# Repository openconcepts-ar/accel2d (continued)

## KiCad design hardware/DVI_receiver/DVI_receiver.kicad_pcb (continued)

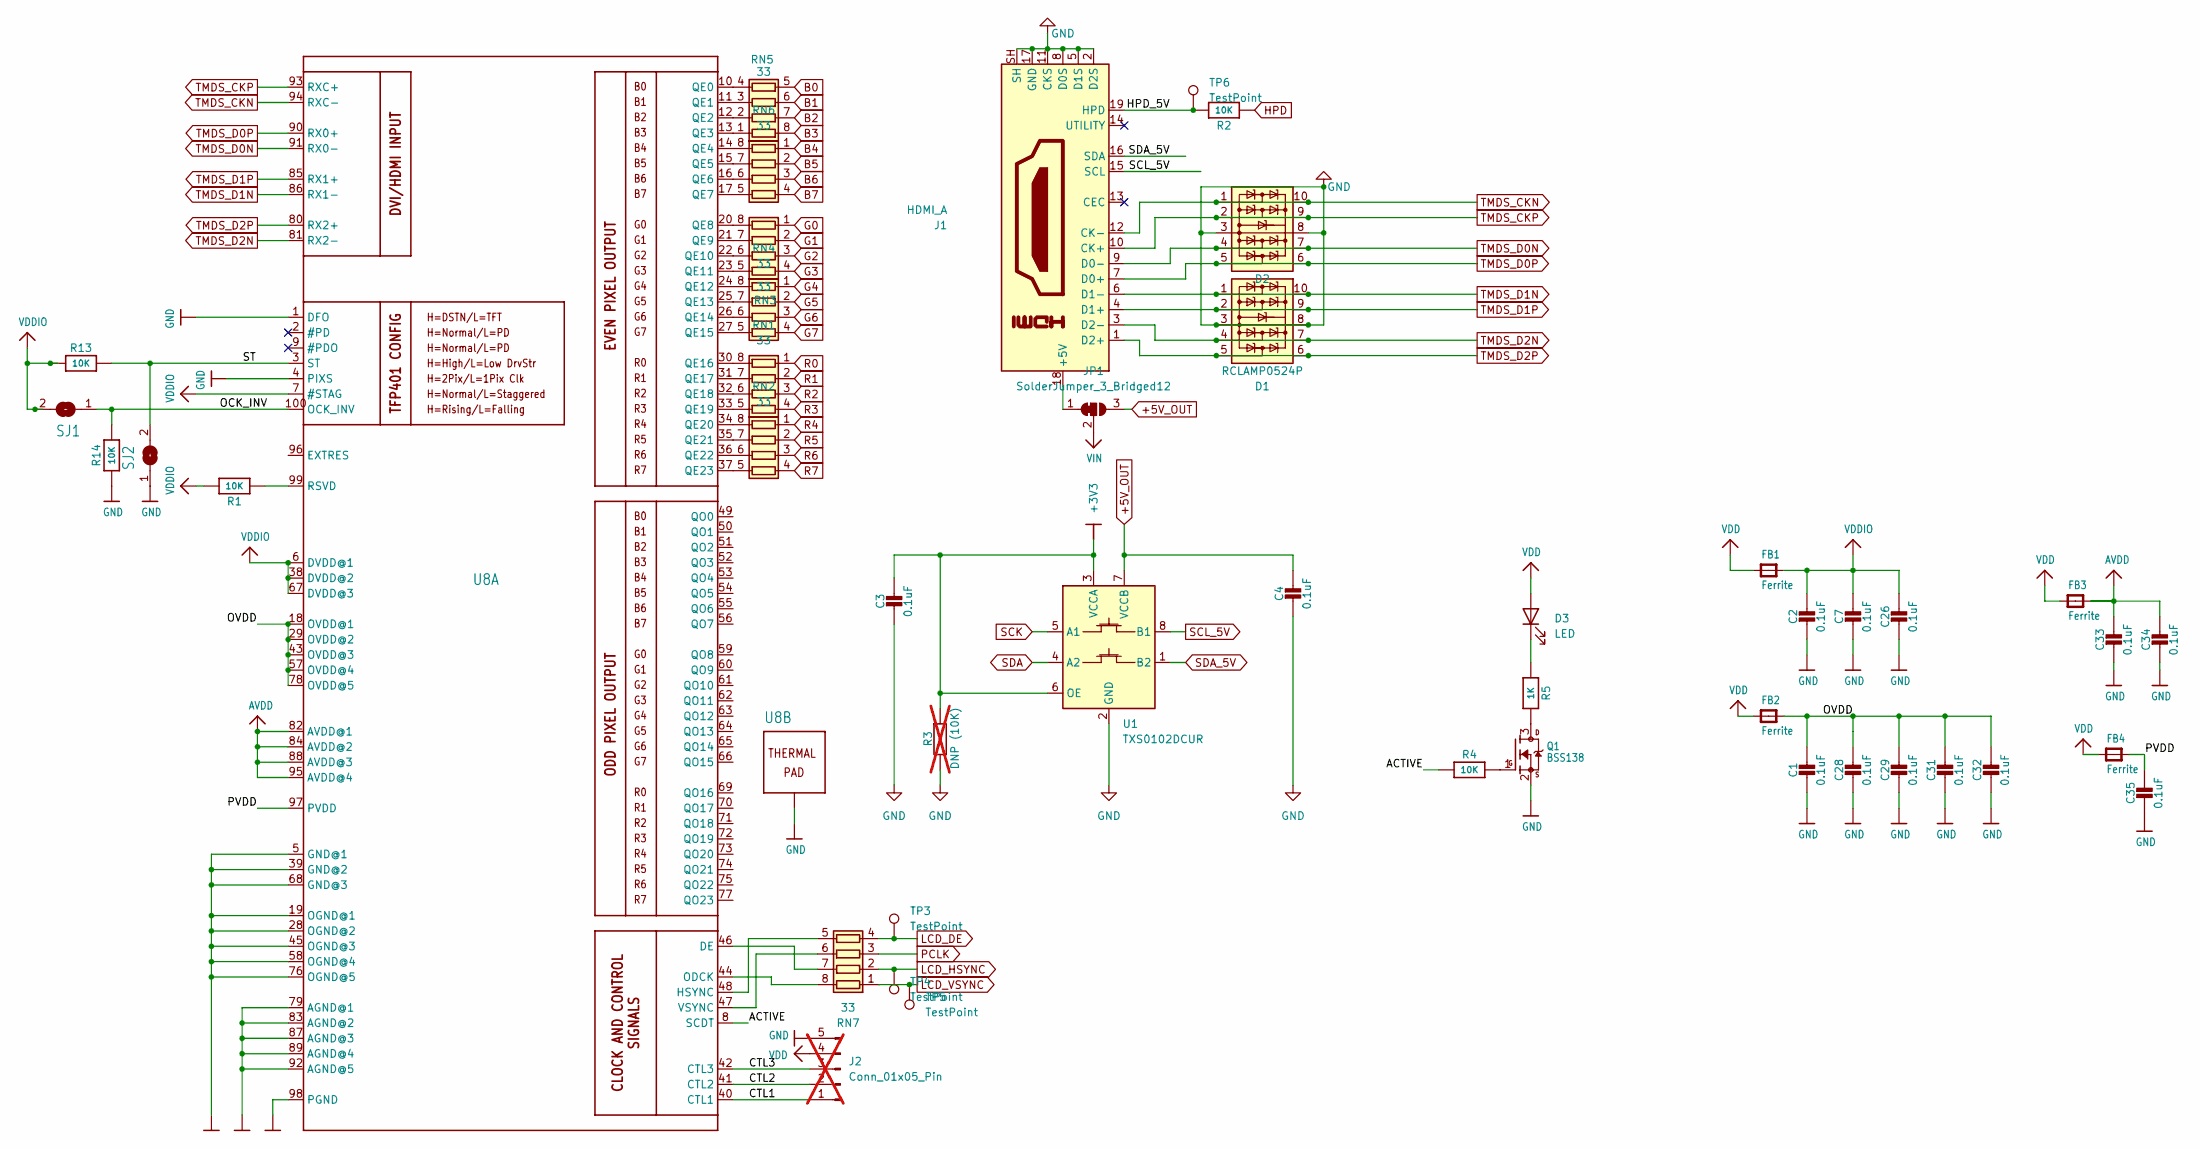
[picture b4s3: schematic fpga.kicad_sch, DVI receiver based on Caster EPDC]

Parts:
C1, C2, C3, C4, C7, C26, C28, C29, C31, C32, C33, C34, C35: 0.1uF; C_0603_1608Metric
D1, D2: RCLAMP0524P; Diodes_UDFN-10_1.0x2.5mm_P0.5mm; MPN RCLAMP0524P
D3: LED; LED_0603_1608Metric
FB1, FB2, FB3, FB4: Ferrite; L_0603_1608Metric; MPN BLM18RK601SN1D
J1: HDMI_A; HDMI_A_Amphenol_10029449-x01xLF_Horizontal; MPN 10029449-111RLF; LCSC Part Number C427307
J2: Conn_01x05_Pin; PinHeader_1x05_P1.27mm_Vertical; not fitted
JP1: SolderJumper_3_Bridged12; SolderJumper-3_P1.3mm_Bridged12_RoundedPad1.0x1.5mm
Q1: BSS138; SOT-323_SC-70; MPN BSS138PW,115
R1, R2, R4, R13, R14: 10K; R_0402_1005Metric
R3: DNP (10K); R_0402_1005Metric; LCSC Part Number C25531; not fitted
R5: 1K; R_0402_1005Metric
RN1, RN2, RN3, RN4, RN5, RN6, RN7: 33; R_Array_Convex_4x0402; MPN YC124-JR-0733RL
SJ1, SJ2: SOLDERJUMPER; SolderJumper-2_P1.3mm_Bridged_RoundedPad1.0x1.5mm
TP3, TP4, TP5, TP6: TestPoint; TestPoint_Pad_D1.0mm
U1: TXS0102DCUR; VSSOP-8_2.3x2mm_P0.5mm; MPN TXS0102DCUR
U8: TFP401; TQFP-100-1EP_14x14mm_P0.5mm_EP5x5mm_ThermalVias; MPN TFP401APZPR

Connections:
+5V_OUT: C4.1, JP1.3 (B), U1.7 (VCCB); also elsewhere on the board
/fpga/ACTIVE: R4.1, U8.8 (SCDT)
/fpga/CTL1: J2.1, U8.40 (CTL1)
/fpga/CTL2: J2.2, U8.41 (CTL2)
/fpga/CTL3: J2.3, U8.42 (CTL3)
/fpga/HPD_5V: J1.19 (HPD), R2.2, TP6.1
/fpga/OCK_INV: R14.2, SJ1.1, U8.100 (OCK_INV)
/fpga/OVDD: C1.1, C28.1, C29.1, C31.1, C32.1, FB2.2, U8.18 (OVDD@1), U8.29 (OVDD@2), U8.43 (OVDD@3), U8.57 (OVDD@4), U8.78 (OVDD@5)
/fpga/PVDD: C35.1, FB4.2, U8.97 (PVDD)
/fpga/ST: R13.2, SJ2.2, U8.3 (ST)
AVDD: C33.1, C34.1, FB3.2, U8.82 (AVDD@1), U8.84 (AVDD@2), U8.88 (AVDD@3), U8.95 (AVDD@4)
B0: RN5.5 (R4.2); also elsewhere on the board
B1: RN5.6 (R3.2); also elsewhere on the board
B2: RN5.7 (R2.2); also elsewhere on the board
B3: RN5.8 (R1.2); also elsewhere on the board
B4: RN6.1 (R1.1); also elsewhere on the board
B5: RN6.2 (R2.1); also elsewhere on the board
B6: RN6.3 (R3.1); also elsewhere on the board
B7: RN6.4 (R4.1); also elsewhere on the board
G0: RN3.1 (R1.1); also elsewhere on the board
G1: RN3.2 (R2.1); also elsewhere on the board
G2: RN3.3 (R3.1); also elsewhere on the board
G3: RN3.4 (R4.1); also elsewhere on the board
G4: RN4.1 (R1.1); also elsewhere on the board
G5: RN4.2 (R2.1); also elsewhere on the board
G6: RN4.3 (R3.1); also elsewhere on the board
G7: RN4.4 (R4.1); also elsewhere on the board
GND: C1.2, C2.2, C3.2, C4.2, C7.2, C26.2, C28.2, C29.2, C31.2, C32.2, C33.2, C34.2, C35.2, D1.3 (GND), D1.8 (GND), D2.3 (GND), D2.8 (GND), J1.2 (D2S), J1.5 (D1S), J1.8 (D0S), J1.11 (CKS), J1.17 (GND), J1.SH, J2.5, Q1.2 (S), R3.2, R14.1, SJ2.1, U1.2 (GND), U8.1 (DFO), U8.4 (PIXS), U8.5 (GND@1), U8.19 (OGND@1), U8.28 (OGND@2), U8.39 (GND@2), U8.45 (OGND@3), U8.58 (OGND@4), U8.68 (GND@3), U8.76 (OGND@5), U8.79 (AGND@1), U8.83 (AGND@2), U8.87 (AGND@3), U8.89 (AGND@4), U8.92 (AGND@5), U8.98 (PGND), U8.P$1 (TP), U8.P$2 (TP), U8.P$3 (TP), U8.P$4 (TP), U8.P$5 (TP), U8.P$6 (TP), U8.P$7 (TP), U8.P$8 (TP), U8.P$9 (TP), U8.P$10 (TP), U8.P$11 (TP), U8.P$12 (TP), U8.P$13 (TP), U8.P$14 (TP), U8.P$15 (TP), U8.P$16 (TP), U8.THERMAL (TP); also elsewhere on the board
HPD: R2.1; also elsewhere on the board
LCD_DE: RN7.4 (R4.1), TP3.1; also elsewhere on the board
LCD_HSYNC: RN7.2 (R2.1), TP4.1; also elsewhere on the board
LCD_VSYNC: RN7.1 (R1.1), TP5.1; also elsewhere on the board
unnamed: D3.1 (K), R5.1
unnamed: J1.18 (+5V), JP1.1 (A)
unnamed: Q1.3 (D), R5.2
unnamed: Q1.1 (G), R4.2
unnamed: RN1.8 (R1.2), U8.30 (QE16)
unnamed: RN1.7 (R2.2), U8.31 (QE17)
unnamed: RN1.6 (R3.2), U8.32 (QE18)
unnamed: RN1.5 (R4.2), U8.33 (QE19)
unnamed: RN2.8 (R1.2), U8.34 (QE20)
unnamed: RN2.7 (R2.2), U8.35 (QE21)
unnamed: RN2.6 (R3.2), U8.36 (QE22)
unnamed: RN2.5 (R4.2), U8.37 (QE23)
unnamed: RN3.8 (R1.2), U8.20 (QE8)
unnamed: RN3.7 (R2.2), U8.21 (QE9)
unnamed: RN3.6 (R3.2), U8.22 (QE10)
unnamed: RN3.5 (R4.2), U8.23 (QE11)
unnamed: RN4.8 (R1.2), U8.24 (QE12)
unnamed: RN4.7 (R2.2), U8.25 (QE13)
unnamed: RN4.6 (R3.2), U8.26 (QE14)
unnamed: RN4.5 (R4.2), U8.27 (QE15)
unnamed: RN5.1 (R1.1), U8.13 (QE3)
unnamed: RN5.2 (R2.1), U8.12 (QE2)
unnamed: RN5.3 (R3.1), U8.11 (QE1)
unnamed: RN5.4 (R4.1), U8.10 (QE0)
unnamed: RN6.8 (R1.2), U8.14 (QE4)
unnamed: RN6.7 (R2.2), U8.15 (QE5)
unnamed: RN6.6 (R3.2), U8.16 (QE6)
unnamed: RN6.5 (R4.2), U8.17 (QE7)
unnamed: RN7.8 (R1.2), U8.44 (ODCK)
unnamed: RN7.7 (R2.2), U8.46 (DE)
unnamed: RN7.6 (R3.2), U8.47 (VSYNC)
unnamed: RN7.5 (R4.2), U8.48 (HSYNC)
unnamed: R1.1, U8.99 (RSVD)
PCLK: RN7.3 (R3.1); also elsewhere on the board
R0: RN1.1 (R1.1); also elsewhere on the board
R1: RN1.2 (R2.1); also elsewhere on the board
R2: RN1.3 (R3.1); also elsewhere on the board
R3: RN1.4 (R4.1); also elsewhere on the board
R4: RN2.1 (R1.1); also elsewhere on the board
R5: RN2.2 (R2.1); also elsewhere on the board
R6: RN2.3 (R3.1); also elsewhere on the board
R7: RN2.4 (R4.1); also elsewhere on the board
SCK: U1.5 (A1); also elsewhere on the board
SCL_5V: J1.15 (SCL), U1.8 (B1)
SDA: U1.4 (A2); also elsewhere on the board
SDA_5V: J1.16 (SDA), U1.1 (B2)
TMDS_CKN: D2.1 (IO1), D2.10 (NC4), J1.12 (CK-), U8.94 (RXC-)
TMDS_CKP: D2.2 (IO2), D2.9 (NC3), J1.10 (CK+), U8.93 (RXC+)
TMDS_D0N: D2.4 (IO3), D2.7 (NC2), J1.9 (D0-), U8.91 (RX0-)
TMDS_D0P: D2.5 (IO4), D2.6 (NC1), J1.7 (D0+), U8.90 (RX0+)
TMDS_D1N: D1.1 (IO1), D1.10 (NC4), J1.6 (D1-), U8.86 (RX1-)
TMDS_D1P: D1.2 (IO2), D1.9 (NC3), J1.4 (D1+), U8.85 (RX1+)
TMDS_D2N: D1.4 (IO3), D1.7 (NC2), J1.3 (D2-), U8.81 (RX2-)
TMDS_D2P: D1.5 (IO4), D1.6 (NC1), J1.1 (D2+), U8.80 (RX2+)
VDDIO: C2.1, C7.1, C26.1, FB1.2, R1.2, R13.1, SJ1.2, U8.6 (DVDD@1), U8.7 (#STAG), U8.38 (DVDD@2), U8.67 (DVDD@3)
VIN: JP1.2 (C); also elsewhere on the board
VIO: C3.1, D3.2 (A), FB1.1, FB2.1, FB3.1, FB4.1, J2.4, R3.1, U1.3 (VCCA), U1.6 (OE); also elsewhere on the board

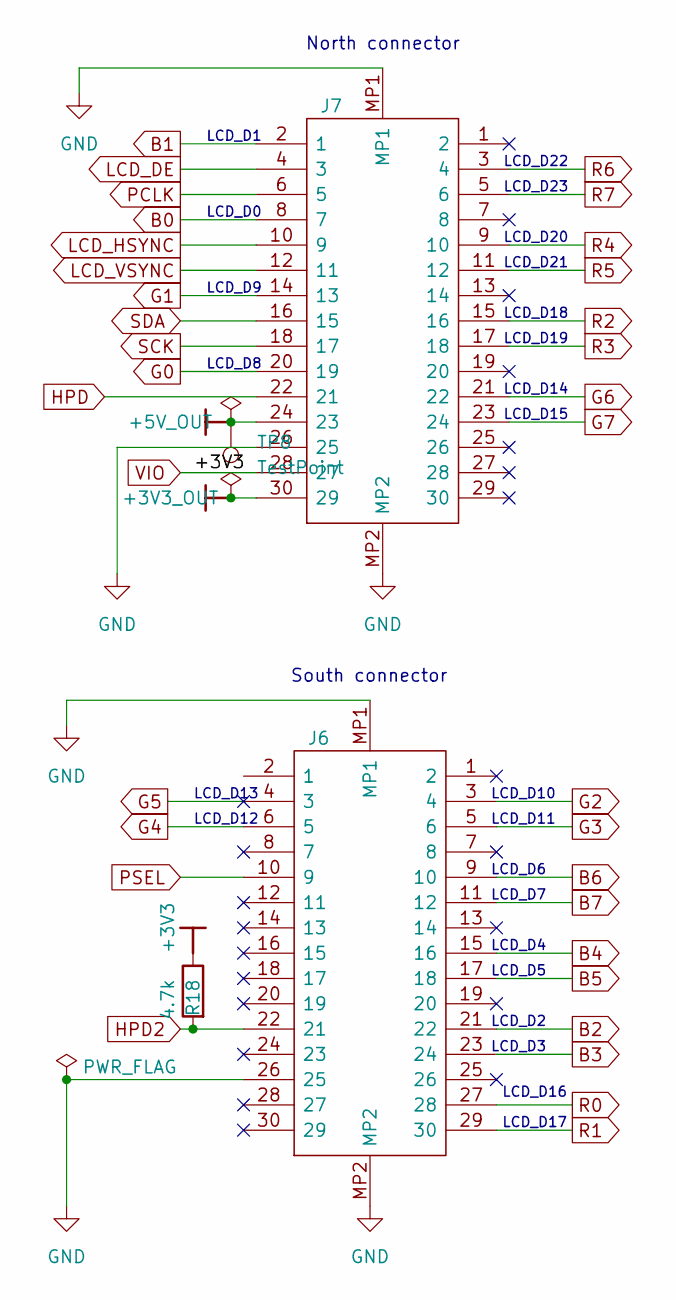
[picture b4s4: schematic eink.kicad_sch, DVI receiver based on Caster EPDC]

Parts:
J6, J7: DF12NB(3.0)-30DS-0.5V(51); DF12NB3030DP05V51; MPN DF12NB(3.0)-30DS-0.5V(51)
R18: 4.7k; R_0402_1005Metric; LCSC Part Number C25940
TP8: TestPoint; TestPoint_Pad_D1.0mm

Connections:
+3V3_OUT: J7.30 (29); also elsewhere on the board
+5V_OUT: J7.24 (23), TP8.1; also elsewhere on the board
B0: J7.8 (7); also elsewhere on the board
B1: J7.2 (1); also elsewhere on the board
B2: J6.21 (22); also elsewhere on the board
B3: J6.23 (24); also elsewhere on the board
B4: J6.15 (16); also elsewhere on the board
B5: J6.17 (18); also elsewhere on the board
B6: J6.9 (10); also elsewhere on the board
B7: J6.11 (12); also elsewhere on the board
G0: J7.20 (19); also elsewhere on the board
G1: J7.14 (13); also elsewhere on the board
G2: J6.3 (4); also elsewhere on the board
G3: J6.5 (6); also elsewhere on the board
G4: J6.6 (5); also elsewhere on the board
G5: J6.4 (3); also elsewhere on the board
G6: J7.21 (22); also elsewhere on the board
G7: J7.23 (24); also elsewhere on the board
GND: J6.26 (25), J6.MP1, J6.MP2, J7.26 (25), J7.MP1, J7.MP2; also elsewhere on the board
HPD: J7.22 (21); also elsewhere on the board
HPD2: J6.22 (21), R18.2
LCD_DE: J7.4 (3); also elsewhere on the board
LCD_HSYNC: J7.10 (9); also elsewhere on the board
LCD_VSYNC: J7.12 (11); also elsewhere on the board
PCLK: J7.6 (5); also elsewhere on the board
PSEL: J6.10 (9)
R0: J6.27 (28); also elsewhere on the board
R1: J6.29 (30); also elsewhere on the board
R2: J7.15 (16); also elsewhere on the board
R3: J7.17 (18); also elsewhere on the board
R4: J7.9 (10); also elsewhere on the board
R5: J7.11 (12); also elsewhere on the board
R6: J7.3 (4); also elsewhere on the board
R7: J7.5 (6); also elsewhere on the board
SCK: J7.18 (17); also elsewhere on the board
SDA: J7.16 (15); also elsewhere on the board
VIO: J7.28 (27), R18.1; also elsewhere on the board

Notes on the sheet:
LCD_D17
LCD_D0
LCD_D16
South connector
LCD_D11
LCD_D4
LCD_D3
LCD_D8
LCD_D10
LCD_D19
LCD_D23
LCD_D20
North connector
LCD_D5
LCD_D13
LCD_D18
LCD_D21
LCD_D22
LCD_D7
LCD_D6
LCD_D15
LCD_D1
LCD_D12
LCD_D9
LCD_D2
LCD_D14

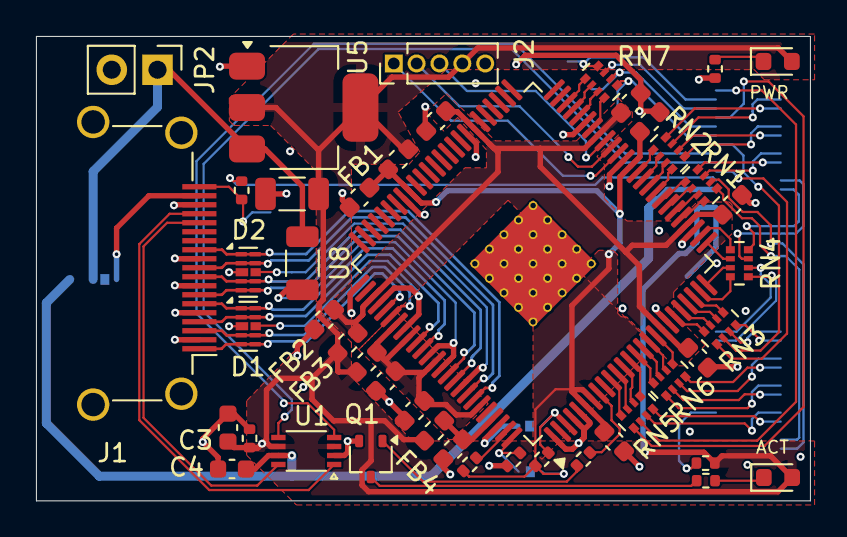
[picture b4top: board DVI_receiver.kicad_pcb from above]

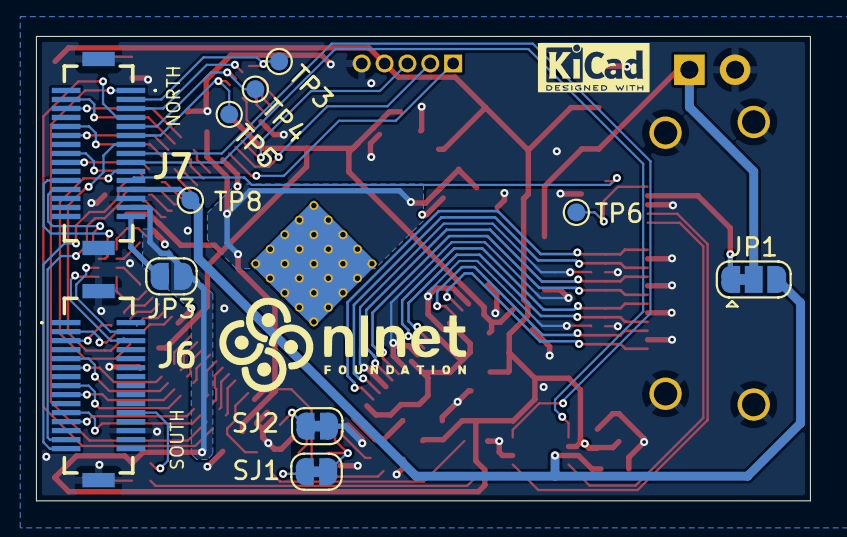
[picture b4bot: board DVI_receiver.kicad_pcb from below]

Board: 4 copper layers, 43.0 x 25.8 mm, 57 parts (11 on the bottom side), 92 nets.

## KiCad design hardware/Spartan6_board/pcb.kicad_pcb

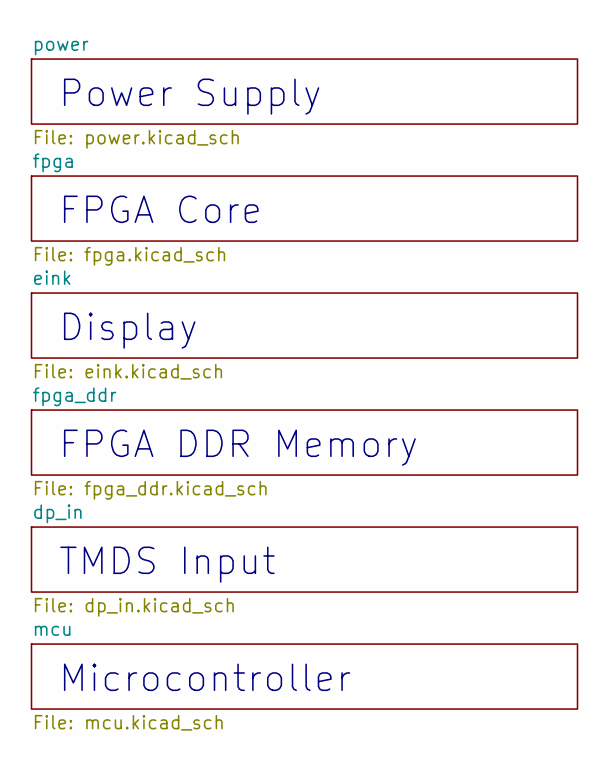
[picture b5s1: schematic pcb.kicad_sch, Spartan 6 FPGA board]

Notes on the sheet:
FPGA DDR Memory
Power Supply
Microcontroller
Display
FPGA Core
TMDS Input

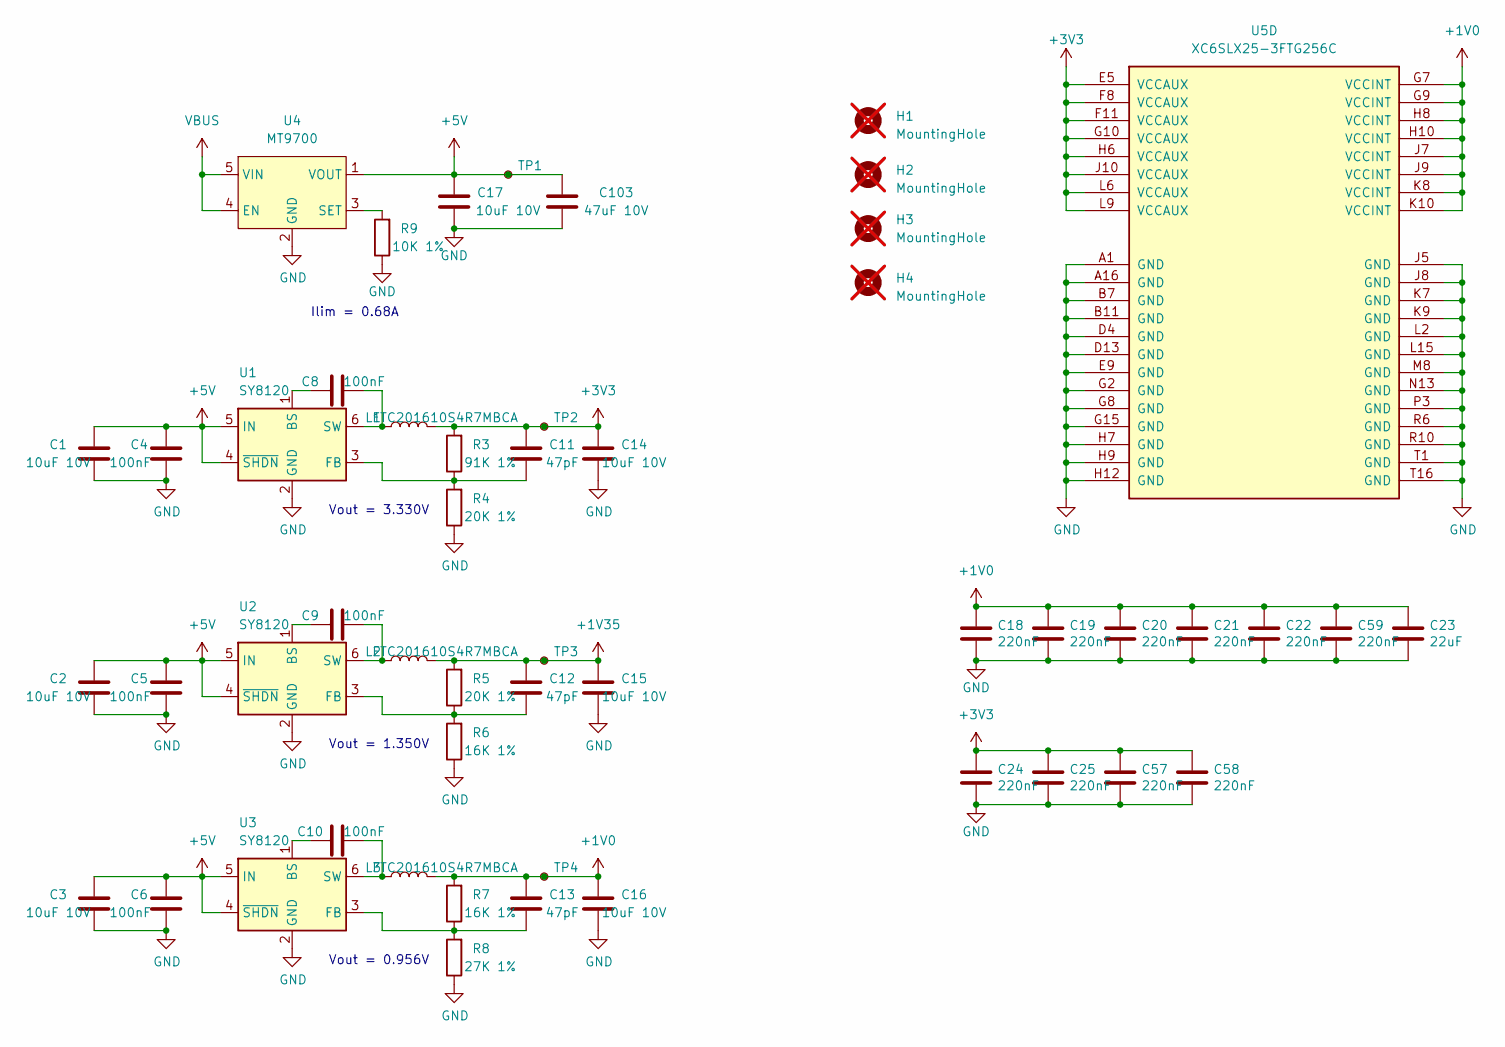
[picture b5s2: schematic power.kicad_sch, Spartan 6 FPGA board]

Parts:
C1, C2, C3, C14, C15, C16: 10uF 10V; C_0805_2012Metric
C4, C5, C6, C8, C9, C10: 100nF; C_0402_1005Metric
C11, C12, C13: 47pF; C_0402_1005Metric
C17: 10uF 10V; C_0805_2012Metric; LCSC Part Number C32635
C18, C19, C20, C21, C22, C24, C25, C57, C58, C59: 220nF; C_0402_1005Metric; LCSC C880414
C23: 22uF; C_0603_1608Metric; LCSC Part Number C86295
C103: 47uF 10V; C_1206_3216Metric; LCSC Part Number C96123
H1, H2, H3, H4: MountingHole; MountingHole_2.2mm_M2_DIN965; not fitted
L1, L2, L3: FTC201610S4R7MBCA; L_Murata_DFE201610P; MPN FTC201610S4R7MBCA
R3: 91K 1%; R_0402_1005Metric
R4, R5: 20K 1%; R_0402_1005Metric; LCSC Part Number WR04X2002FTL
R6, R7: 16K 1%; R_0402_1005Metric
R8: 27K 1%; R_0402_1005Metric
R9: 10K 1%; R_0402_1005Metric
TP1, TP2, TP3, TP4: TestPoint_Small; TestPoint_Pad_D1.5mm
U1, U2, U3: SY8120; SOT-23-6; MPN SY8120IABC
U4: MT9700; SOT-23-5; MPN MT9700
U5: XC6SLX25-3FTG256C; Xilinx_FTG256; LCSC Part Number C1521716

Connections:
+1V0: C13.2, C16.2, C18.1, C19.1, C20.1, C21.1, C22.1, C23.1, C59.1, L3.2, R7.2, TP4.1, U5.G7 (VCCINT), U5.G9 (VCCINT), U5.H8 (VCCINT), U5.H10 (VCCINT), U5.J7 (VCCINT), U5.J9 (VCCINT), U5.K8 (VCCINT), U5.K10 (VCCINT)
+1V35: C12.2, C15.2, L2.2, R5.2, TP3.1; also elsewhere on the board
+3V3: C11.2, C14.2, C24.1, C25.1, C57.1, C58.1, L1.2, R3.2, TP2.1, U5.E5 (VCCAUX), U5.F8 (VCCAUX), U5.F11 (VCCAUX), U5.G10 (VCCAUX), U5.H6 (VCCAUX), U5.J10 (VCCAUX), U5.L6 (VCCAUX), U5.L9 (VCCAUX); also elsewhere on the board
+5V: C1.2, C2.2, C3.2, C4.2, C5.2, C6.2, C17.2, C103.2, TP1.1, U1.4 (~SHDN), U1.5 (IN), U2.4 (~SHDN), U2.5 (IN), U3.4 (~SHDN), U3.5 (IN), U4.1 (VOUT); also elsewhere on the board
GND: C1.1, C2.1, C3.1, C4.1, C5.1, C6.1, C14.1, C15.1, C16.1, C17.1, C18.2, C19.2, C20.2, C21.2, C22.2, C23.2, C24.2, C25.2, C57.2, C58.2, C59.2, C103.1, R4.1, R6.1, R8.1, R9.1, U1.2 (GND), U2.2 (GND), U3.2 (GND), U4.2 (GND), U5.A1 (GND), U5.A16 (GND), U5.B7 (GND), U5.B11 (GND), U5.D4 (GND), U5.D13 (GND), U5.E9 (GND), U5.G2 (GND), U5.G8 (GND), U5.G15 (GND), U5.H7 (GND), U5.H9 (GND), U5.H12 (GND), U5.J5 (GND), U5.J8 (GND), U5.K7 (GND), U5.K9 (GND), U5.L2 (GND), U5.L15 (GND), U5.M8 (GND), U5.N13 (GND), U5.P3 (GND), U5.R6 (GND), U5.R10 (GND), U5.T1 (GND), U5.T16 (GND); also elsewhere on the board
unnamed: C8.2, U1.1 (BS)
unnamed: C11.1, R3.1, R4.2, U1.3 (FB)
unnamed: C8.1, L1.1, U1.6 (SW)
unnamed: C9.2, U2.1 (BS)
unnamed: C12.1, R5.1, R6.2, U2.3 (FB)
unnamed: C9.1, L2.1, U2.6 (SW)
unnamed: C10.2, U3.1 (BS)
unnamed: C13.1, R7.1, R8.2, U3.3 (FB)
unnamed: C10.1, L3.1, U3.6 (SW)
unnamed: R9.2, U4.3 (SET)
VBUS: U4.4 (EN), U4.5 (VIN); also elsewhere on the board

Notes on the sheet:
Vout = 1.350V
Ilim = 0.68A
Vout = 0.956V
Vout = 3.330V

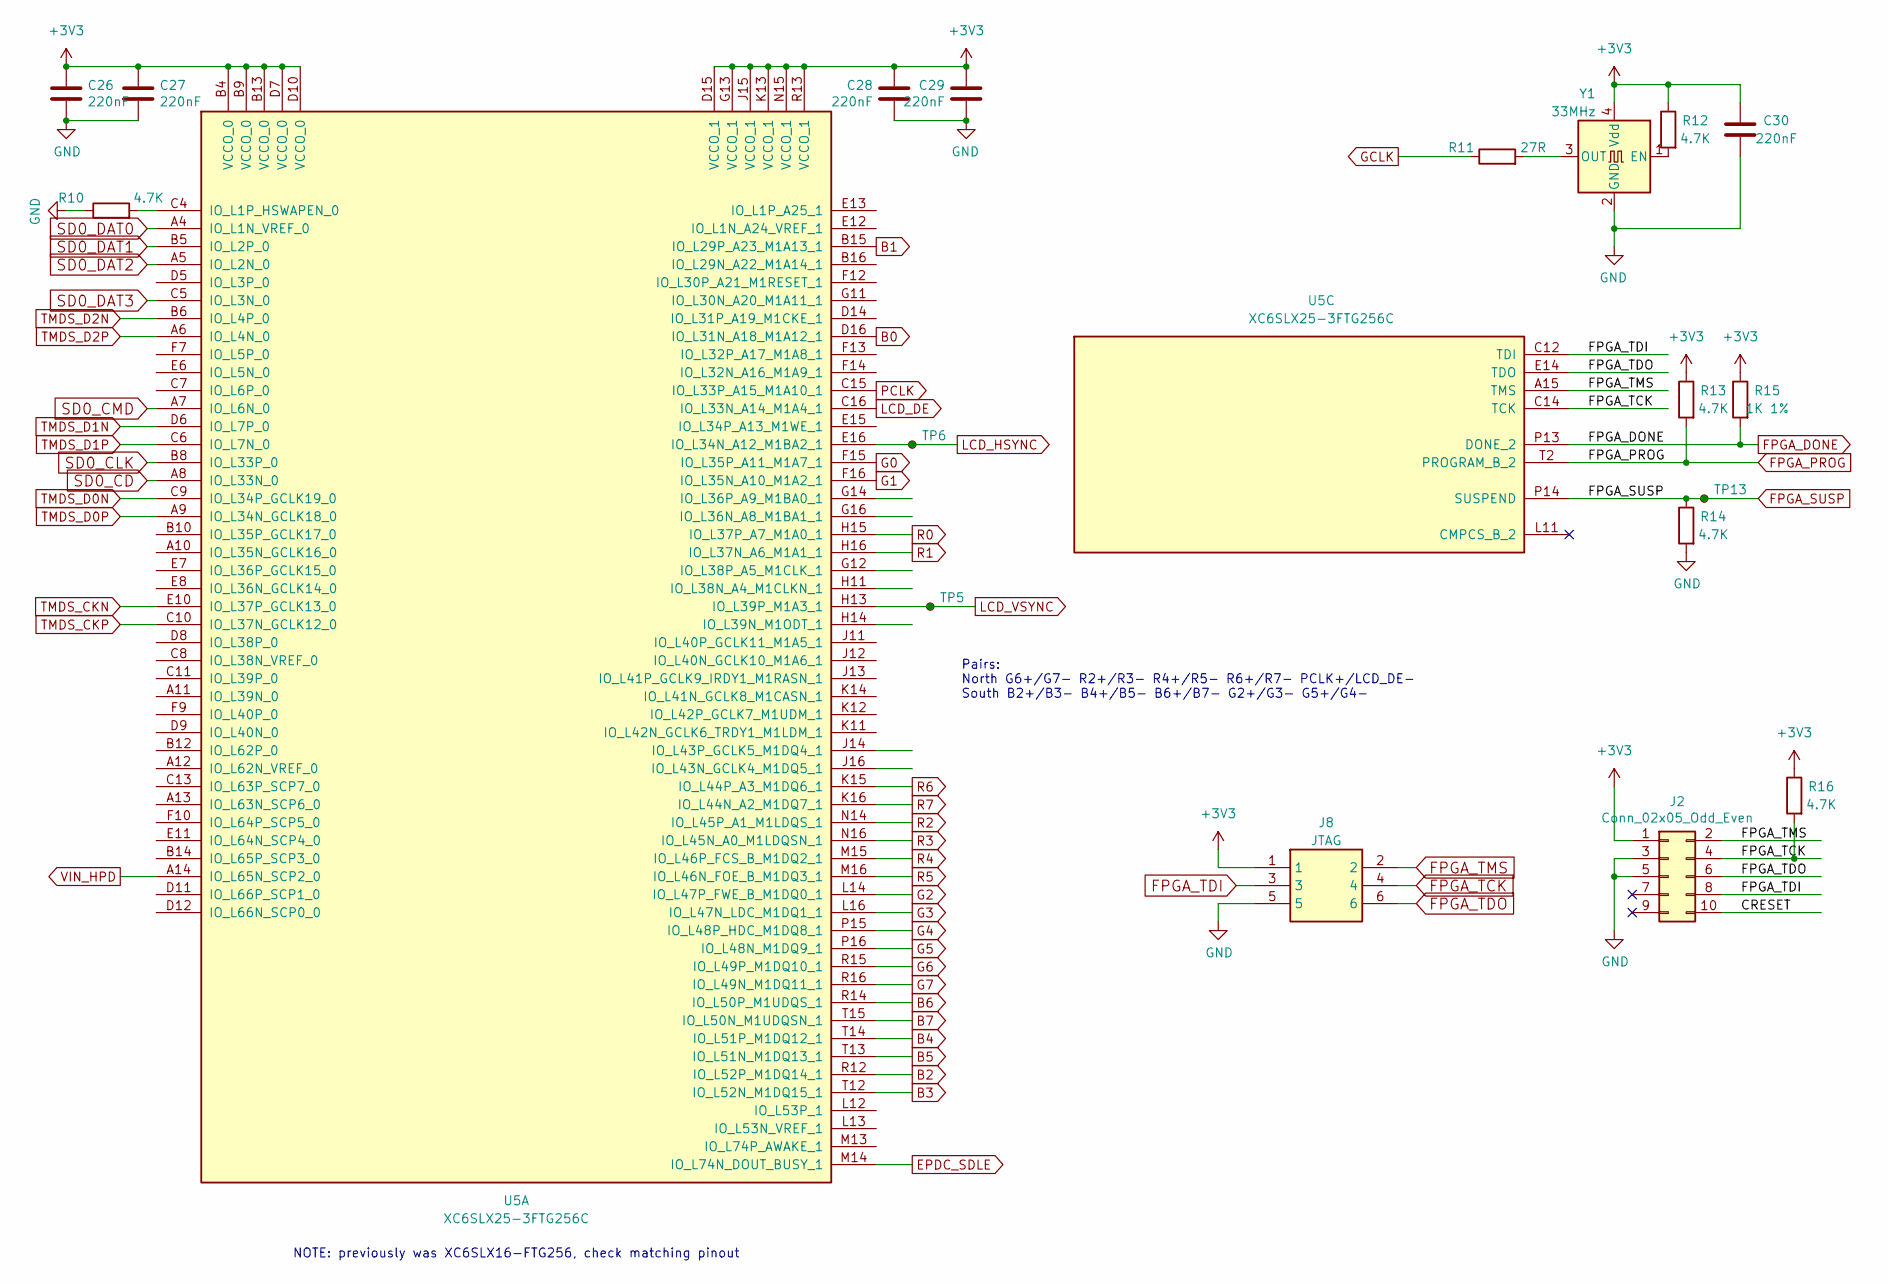
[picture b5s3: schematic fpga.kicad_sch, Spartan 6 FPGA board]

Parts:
C26, C27, C28, C29, C30: 220nF; C_0402_1005Metric; LCSC C880414
J2: Conn_02x05_Odd_Even; PinHeader_2x05_P1.27mm_Vertical_SMD
J8: JTAG; Tag-Connect_TC2030-IDC-NL_2x03_P1.27mm_Vertical; Mouser Part Number 474-PRT-12807; LCSC Part Number DNP
R10, R12, R13, R14, R16: 4.7K; R_0402_1005Metric; LCSC C105870
R11: 27R; R_0402_1005Metric; LCSC C93929
R15: 1K 1%; R_0402_1005Metric
TP5, TP6, TP13: TestPoint_Small; TestPoint_Pad_D1.5mm
U5: XC6SLX25-3FTG256C; Xilinx_FTG256; LCSC Part Number C1521716
Y1: 33MHz; Oscillator_SMD_Abracon_ASE-4Pin_3.2x2.5mm; MPN 3N24000G33YC; LCSC Part Number C252339

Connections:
+3V3: C26.1, C27.1, C28.1, C29.1, C30.2, J2.1, J8.1, R12.1, R13.1, R15.1, R16.1, U5.B4 (VCCO_0), U5.B9 (VCCO_0), U5.B13 (VCCO_0), U5.D7 (VCCO_0), U5.D10 (VCCO_0), U5.D15 (VCCO_1), U5.G13 (VCCO_1), U5.J15 (VCCO_1), U5.K13 (VCCO_1), U5.N15 (VCCO_1), U5.R13 (VCCO_1), Y1.4 (Vdd); also elsewhere on the board
B0: U5.D16 (IO_L31N_A18_M1A12_1); also elsewhere on the board
B1: U5.B15 (IO_L29P_A23_M1A13_1); also elsewhere on the board
B2: U5.R12 (IO_L52P_M1DQ14_1); also elsewhere on the board
B3: U5.T12 (IO_L52N_M1DQ15_1); also elsewhere on the board
B4: U5.T14 (IO_L51P_M1DQ12_1); also elsewhere on the board
B5: U5.T13 (IO_L51N_M1DQ13_1); also elsewhere on the board
B6: U5.R14 (IO_L50P_M1UDQS_1); also elsewhere on the board
B7: U5.T15 (IO_L50N_M1UDQSN_1); also elsewhere on the board
EPDC_SDLE: U5.M14 (IO_L74N_DOUT_BUSY_1)
FPGA_DONE: R15.2, U5.A14 (IO_L65N_SCP2_0), U5.P13 (DONE_2); also elsewhere on the board
FPGA_PROG: R13.2, U5.T2 (PROGRAM_B_2); also elsewhere on the board
FPGA_SUSP: R14.1, TP13.1, U5.P14 (SUSPEND); also elsewhere on the board
FPGA_TCK: J2.4, J8.4, R16.2, U5.C14 (TCK)
FPGA_TDI: J2.8, J8.3, U5.C12 (TDI)
FPGA_TDO: J2.6, J8.6, U5.E14 (TDO)
FPGA_TMS: J2.2, J8.2, U5.A15 (TMS)
G0: U5.F15 (IO_L35P_A11_M1A7_1); also elsewhere on the board
G1: U5.F16 (IO_L35N_A10_M1A2_1); also elsewhere on the board
G2: U5.L14 (IO_L47P_FWE_B_M1DQ0_1); also elsewhere on the board
G3: U5.L16 (IO_L47N_LDC_M1DQ1_1); also elsewhere on the board
G4: U5.P15 (IO_L48P_HDC_M1DQ8_1); also elsewhere on the board
G5: U5.P16 (IO_L48N_M1DQ9_1); also elsewhere on the board
G6: U5.R15 (IO_L49P_M1DQ10_1); also elsewhere on the board
G7: U5.R16 (IO_L49N_M1DQ11_1); also elsewhere on the board
GCLK: R11.1; also elsewhere on the board
GND: C26.2, C27.2, C28.2, C29.2, C30.1, J2.3, J2.5, J8.5, R10.1, R14.2, Y1.2 (GND); also elsewhere on the board
LCD_DE: U5.C16 (IO_L33N_A14_M1A4_1); also elsewhere on the board
LCD_HSYNC: TP6.1, U5.E16 (IO_L34N_A12_M1BA2_1); also elsewhere on the board
LCD_VSYNC: TP5.1, U5.H13 (IO_L39P_M1A3_1); also elsewhere on the board
unnamed: R10.2, U5.C4 (IO_L1P_HSWAPEN_0)
unnamed: R12.2, Y1.1 (EN)
unnamed: R11.2, Y1.3 (OUT)
PCLK: U5.C15 (IO_L33P_A15_M1A10_1); also elsewhere on the board
R2: U5.N14 (IO_L45P_A1_M1LDQS_1); also elsewhere on the board
R3: U5.N16 (IO_L45N_A0_M1LDQSN_1); also elsewhere on the board
R4: U5.M15 (IO_L46P_FCS_B_M1DQ2_1); also elsewhere on the board
R5: U5.M16 (IO_L46N_FOE_B_M1DQ3_1); also elsewhere on the board
R6: U5.K15 (IO_L44P_A3_M1DQ6_1); also elsewhere on the board
R7: U5.K16 (IO_L44N_A2_M1DQ7_1); also elsewhere on the board
SD0_CD: U5.A8 (IO_L33N_0); also elsewhere on the board
SD0_CLK: U5.B8 (IO_L33P_0); also elsewhere on the board
SD0_CMD: U5.A7 (IO_L6N_0); also elsewhere on the board
SD0_DAT0: U5.A4 (IO_L1N_VREF_0); also elsewhere on the board
SD0_DAT1: U5.B5 (IO_L2P_0); also elsewhere on the board
SD0_DAT2: U5.A5 (IO_L2N_0); also elsewhere on the board
SD0_DAT3: U5.C5 (IO_L3N_0); also elsewhere on the board
TMDS_CKN: U5.E10 (IO_L37P_GCLK13_0); also elsewhere on the board
TMDS_CKP: U5.C10 (IO_L37N_GCLK12_0); also elsewhere on the board
TMDS_D0N: U5.C9 (IO_L34P_GCLK19_0); also elsewhere on the board
TMDS_D0P: U5.A9 (IO_L34N_GCLK18_0); also elsewhere on the board
TMDS_D1N: U5.D6 (IO_L7P_0); also elsewhere on the board
TMDS_D1P: U5.C6 (IO_L7N_0); also elsewhere on the board
TMDS_D2N: U5.B6 (IO_L4P_0); also elsewhere on the board
TMDS_D2P: U5.A6 (IO_L4N_0); also elsewhere on the board

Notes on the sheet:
Pairs: North G6+/G7- R2+/R3- R4+/R5- R6+/R7- PCLK+/LCD_DE- South B2+/B3- B4+/B5- B6+/B7- G2+/G3- G5+/G4-
NOTE: previously was XC6SLX16-FTG256, check matching pinout

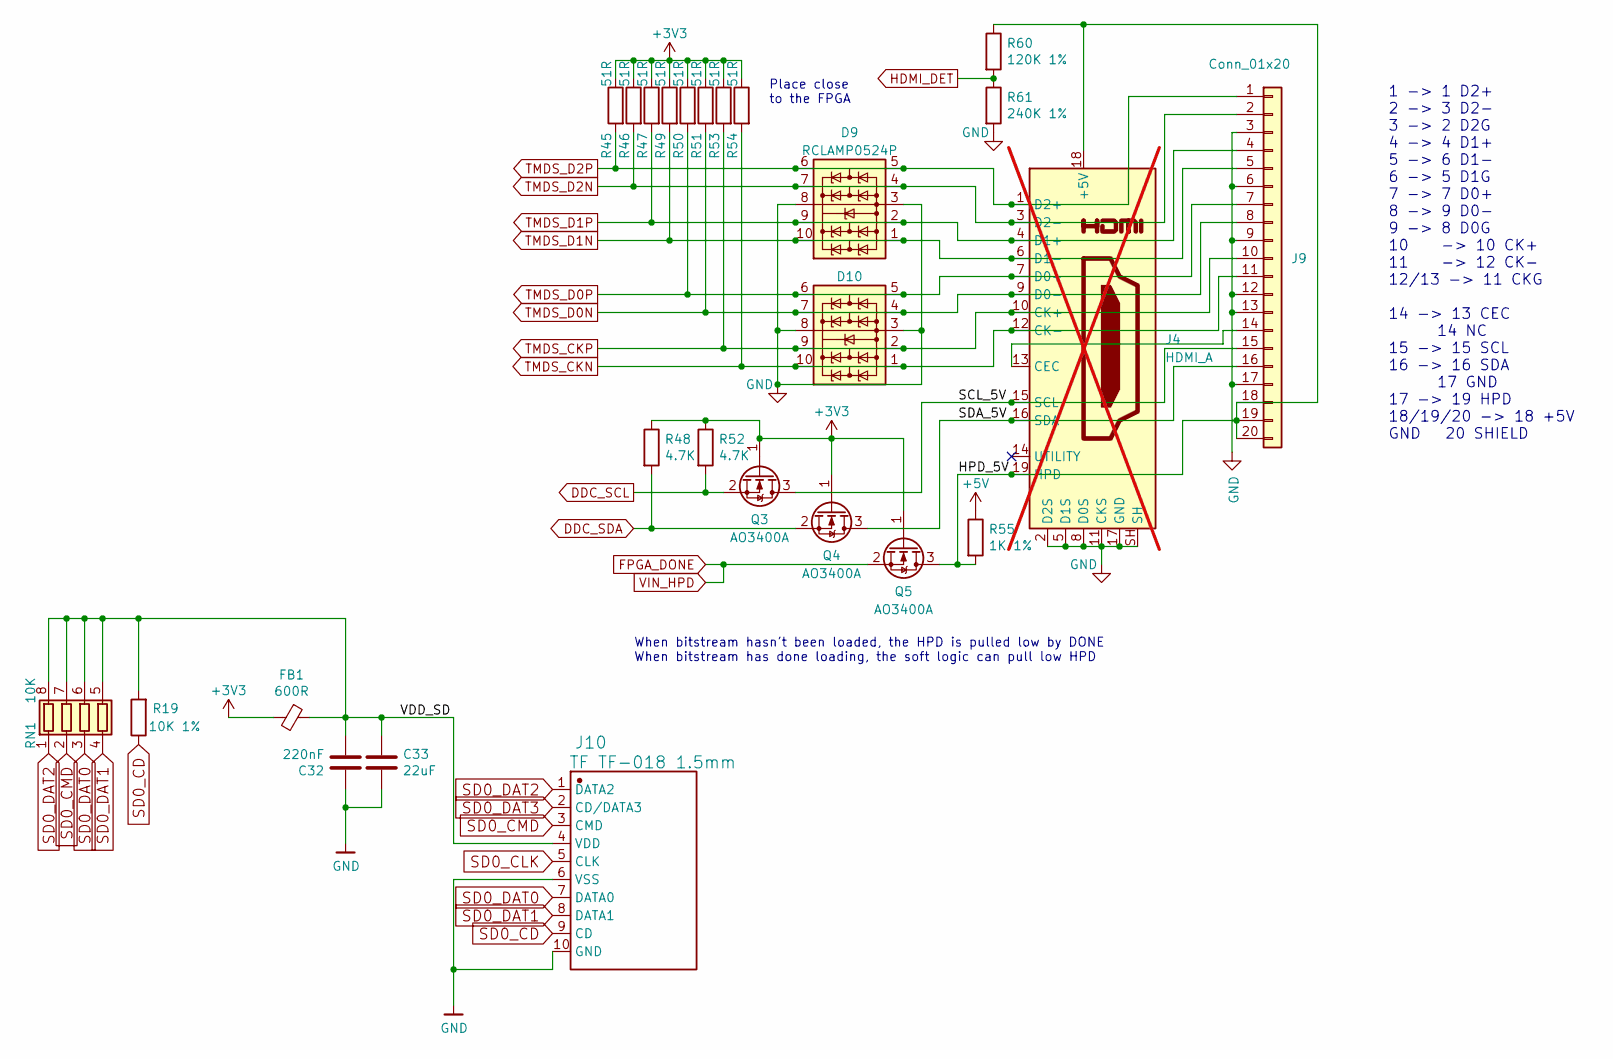
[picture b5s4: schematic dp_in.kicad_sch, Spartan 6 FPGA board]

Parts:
C32: 220nF; C_0402_1005Metric; LCSC C880414
C33: 22uF; C_0603_1608Metric; LCSC Part Number C86295
D9, D10: RCLAMP0524P; Diodes_UDFN-10_1.0x2.5mm_P0.5mm; MPN RCLAMP0524P
FB1: 600R; L_0402_1005Metric; MPN BLM15AG601SN1D
J4: HDMI_A; HDMI_A_Molex_208658-1001_Horizontal; MPN 2086581001; not fitted
J9: Conn_01x20; FPC-SMD_20P-P0.50_L4.4-W15.6; MPN F0501-B-20-20T-R
J10: TF TF-018 1.5mm; TF-SMD_TF-018; MPN TF-018
Q3, Q4, Q5: AO3400A; SOT-23; MPN AO3400A
R19: 10K 1%; R_0402_1005Metric
R45, R46, R47, R49, R50, R51, R53, R54: 51R; R_0402_1005Metric; LCSC C105870
R48, R52: 4.7K; R_0402_1005Metric
R55: 1K 1%; R_0402_1005Metric
R60: 120K 1%; R_0402_1005Metric
R61: 240K 1%; R_0402_1005Metric
RN1: 10K; R_Array_Convex_4x0402; MPN 4D02WGJ0103TCE

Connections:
+3V3: FB1.2, Q3.1 (G), Q4.1 (G), Q5.1 (G), R45.1, R46.1, R47.1, R48.1, R49.1, R50.1, R51.1, R52.1, R53.1, R54.1; also elsewhere on the board
+5V: R55.1; also elsewhere on the board
/dp_in/HPD_5V: J4.18 (+5V), J4.19 (HPD), J9.18, J9.19, J9.20, Q5.3 (D), R55.2, R60.1
/dp_in/SCL_5V: J4.15 (SCL), J9.15, Q3.3 (D)
/dp_in/SDA_5V: J4.16 (SDA), J9.16, Q4.3 (D)
/dp_in/VDD_SD: C32.2, C33.1, FB1.1, J10.4 (VDD), R19.2, RN1.5 (R4.2), RN1.6 (R3.2), RN1.7 (R2.2), RN1.8 (R1.2)
DDC_SCL: Q3.2 (S), R52.2; also elsewhere on the board
DDC_SDA: Q4.2 (S), R48.2; also elsewhere on the board
FPGA_DONE: Q5.2 (S); also elsewhere on the board
GND: C32.1, C33.2, D9.3 (GND), D9.8 (GND), D10.3 (GND), D10.8 (GND), J4.2 (D2S), J4.5 (D1S), J4.8 (D0S), J4.11 (CKS), J4.17 (GND), J4.SH, J9.3, J9.6, J9.9, J9.12, J9.13, J9.17, J10.6 (VSS), J10.10 (GND), R61.2; also elsewhere on the board
HDMI_DET: R60.2, R61.1; also elsewhere on the board
unnamed: J4.13 (CEC), J9.14
SD0_CD: J10.9 (CD), R19.1; also elsewhere on the board
SD0_CLK: J10.5 (CLK); also elsewhere on the board
SD0_CMD: J10.3 (CMD), RN1.2 (R2.1); also elsewhere on the board
SD0_DAT0: J10.7 (DATA0), RN1.3 (R3.1); also elsewhere on the board
SD0_DAT1: J10.8 (DATA1), RN1.4 (R4.1); also elsewhere on the board
SD0_DAT2: J10.1 (DATA2), RN1.1 (R1.1); also elsewhere on the board
SD0_DAT3: J10.2 (CD/DATA3); also elsewhere on the board
TMDS_CKN: D10.1 (IO1), D10.10 (NC4), J4.12 (CK-), J9.11, R54.2; also elsewhere on the board
TMDS_CKP: D10.2 (IO2), D10.9 (NC3), J4.10 (CK+), J9.10, R53.2; also elsewhere on the board
TMDS_D0N: D10.4 (IO3), D10.7 (NC2), J4.9 (D0-), J9.8, R51.2; also elsewhere on the board
TMDS_D0P: D10.5 (IO4), D10.6 (NC1), J4.7 (D0+), J9.7, R50.2; also elsewhere on the board
TMDS_D1N: D9.1 (IO1), D9.10 (NC4), J4.6 (D1-), J9.5, R49.2; also elsewhere on the board
TMDS_D1P: D9.2 (IO2), D9.9 (NC3), J4.4 (D1+), J9.4, R47.2; also elsewhere on the board
TMDS_D2N: D9.4 (IO3), D9.7 (NC2), J4.3 (D2-), J9.2, R46.2; also elsewhere on the board
TMDS_D2P: D9.5 (IO4), D9.6 (NC1), J4.1 (D2+), J9.1, R45.2; also elsewhere on the board

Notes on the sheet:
1 -> 1 D2+ 2 -> 3 D2- 3 -> 2 D2G 4 -> 4 D1+ 5 -> 6 D1- 6 -> 5 D1G 7 -> 7 D0+ 8 -> 9 D0- 9 -> 8 D0G 10 -> 10 CK+ 11 -> 12 CK- 12/13 -> 11 CKG 14 -> 13 CEC 14 NC 15 -> 15 SCL 16 -> 16 SDA 17 GND 17 -> 19 HPD 18/19/20 -> 18 +5V GND 20 SHIELD
Place close to the FPGA
When bitstream hasn't been loaded, the HPD is pulled low by DONE When bitstream has done loading, the soft logic can pull low HPD
